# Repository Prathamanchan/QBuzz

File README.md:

# QBuzz
QBuzz Final Project 
Upload the code to arduino and run

$ python qbuzz.py

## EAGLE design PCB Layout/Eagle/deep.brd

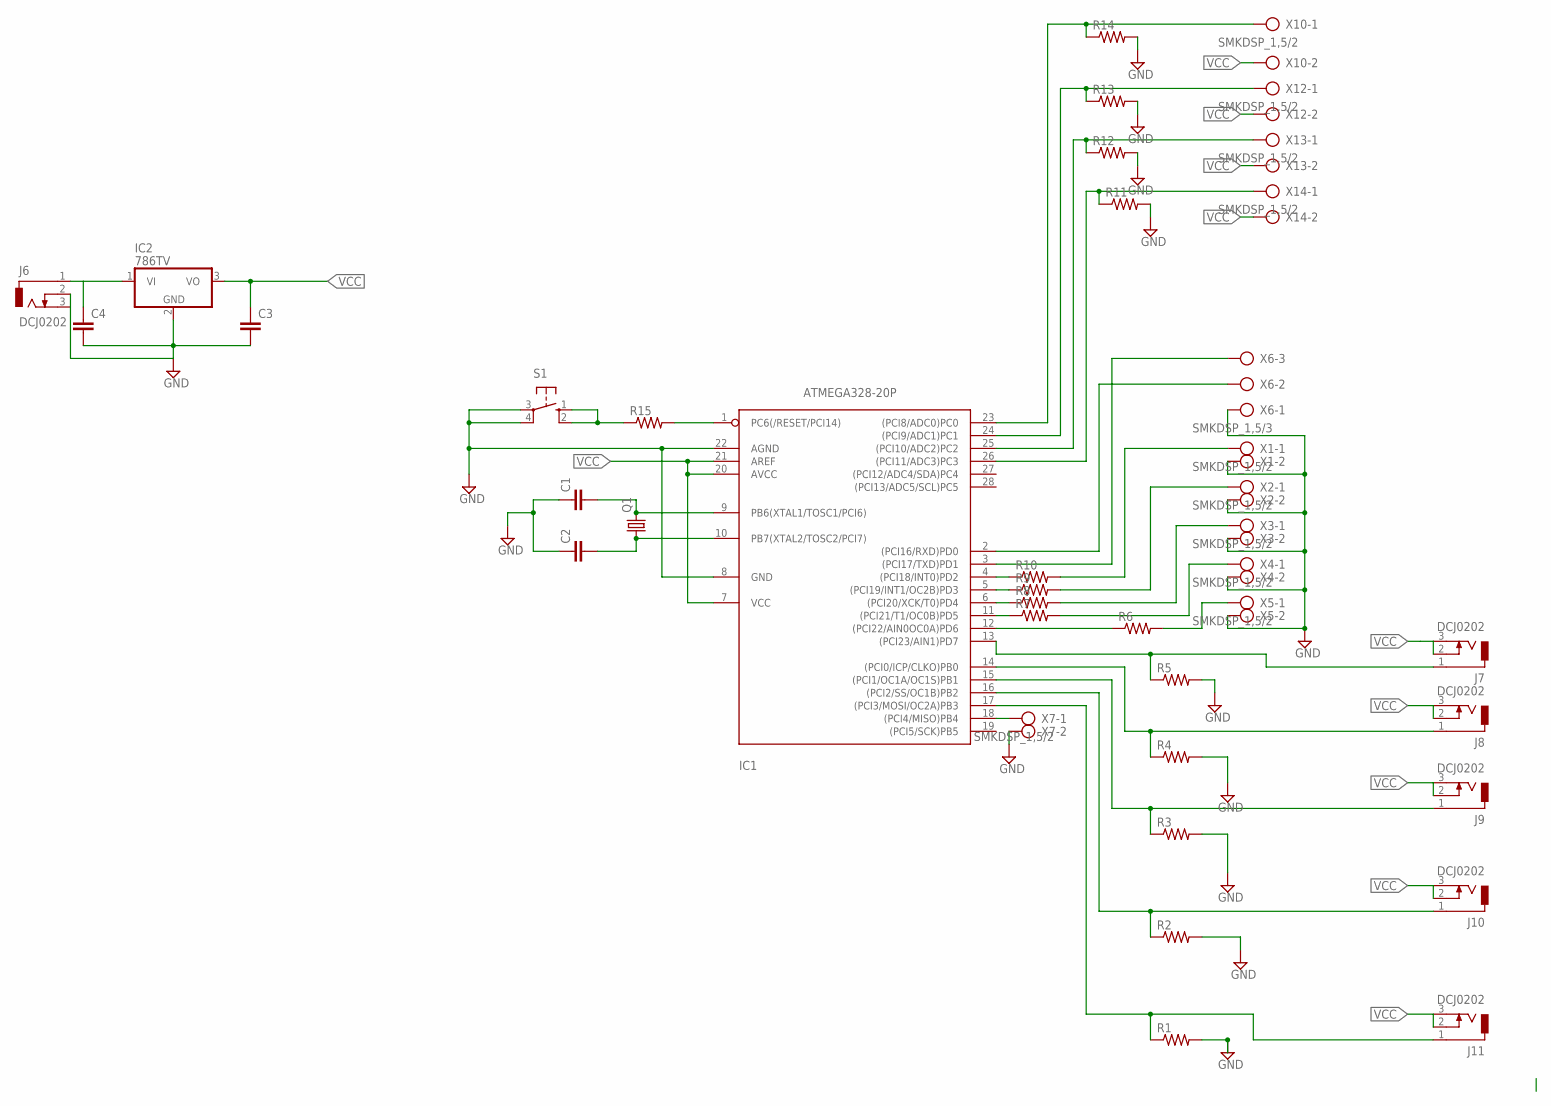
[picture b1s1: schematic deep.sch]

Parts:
C1, C2: C-EU025-030X050; C025-030X050
C3, C4: C-EU025-025X050; C025-025X050
IC1: ATMEGA328-20P; DIL28-3
IC2: 786TV; TO220V
J6, J7, J8, J9, J10, J11: DCJ0202
Q1: CRYSTALHC49U70; HC49U70
R1, R2, R3, R4, R5, R6, R7, R8, R9, R10, R11, R12, R13, R14, R15: R-US_0207/10; 0207/10
S1: 10-XX; B3F-10XX
X1, X2, X3, X4, X5, X7, X10, X12, X13, X14: SMKDSP_1,5/2
X6: SMKDSP_1,5/3

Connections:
GND: C1.1, C2.1, C3.2, C4.2, IC1.8 (GND), IC1.22 (AGND), IC2.2 (GND), J6.2, J6.3, R1.2, R2.2, R3.2, R4.2, R5.2, R11.2, R12.2, R13.2, R14.2, S1.3, S1.4 (P1), X1.2, X2.2, X3.2, X4.2, X5.2, X6.1, X7.2
unnamed: C1.2, IC1.9 (PB6(XTAL1/TOSC1/PCI6)), Q1.2
unnamed: C2.2, IC1.10 (PB7(XTAL2/TOSC2/PCI7)), Q1.1
unnamed: IC1.1 (PC6(/RESET/PCI14)), R15.2
unnamed: R15.1, S1.1 (S), S1.2 (S1)
unnamed: IC1.12 ((PCI22/AIN0OC0A)PD6), R6.1
unnamed: IC1.11 ((PCI21/T1/OC0B)PD5), R7.1
unnamed: IC1.6 ((PCI20/XCK/T0)PD4), R8.1
unnamed: IC1.5 ((PCI19/INT1/OC2B)PD3), R9.1
unnamed: IC1.4 ((PCI18/INT0)PD2), R10.1
unnamed: IC1.2 ((PCI16/RXD)PD0), X6.2
unnamed: IC1.14 ((PCI0/ICP/CLKO)PB0), J8.1, R4.1
unnamed: IC1.15 ((PCI1/OC1A/OC1S)PB1), J9.1, R3.1
unnamed: IC1.16 ((PCI2/SS/OC1B)PB2), J10.1, R2.1
unnamed: IC1.17 ((PCI3/MOSI/OC2A)PB3), J11.1, R1.1
unnamed: R10.2, X1.1
unnamed: R9.2, X2.1
unnamed: R8.2, X3.1
unnamed: R7.2, X4.1
unnamed: R6.2, X5.1
unnamed: IC1.3 ((PCI17/TXD)PD1), X6.3
unnamed: IC1.24 ((PCI9/ADC1)PC1), R13.1, X12.1
unnamed: IC1.13 ((PCI23/AIN1)PD7), J7.1, R5.1
unnamed: C4.1, IC2.1 (VI), J6.1
unnamed: IC1.18 ((PCI4/MISO)PB4), X7.1
unnamed: IC1.23 ((PCI8/ADC0)PC0), R14.1, X10.1
unnamed: J7.2, J7.3
unnamed: IC1.25 ((PCI10/ADC2)PC2), R12.1, X13.1
unnamed: IC1.26 ((PCI11/ADC3)PC3), R11.1, X14.1
VCC: C3.1, IC1.7 (VCC), IC1.20 (AVCC), IC1.21 (AREF), IC2.3 (VO), J8.2, J8.3, J9.2, J9.3, J10.2, J10.3, J11.2, J11.3, X10.2, X12.2, X13.2, X14.2

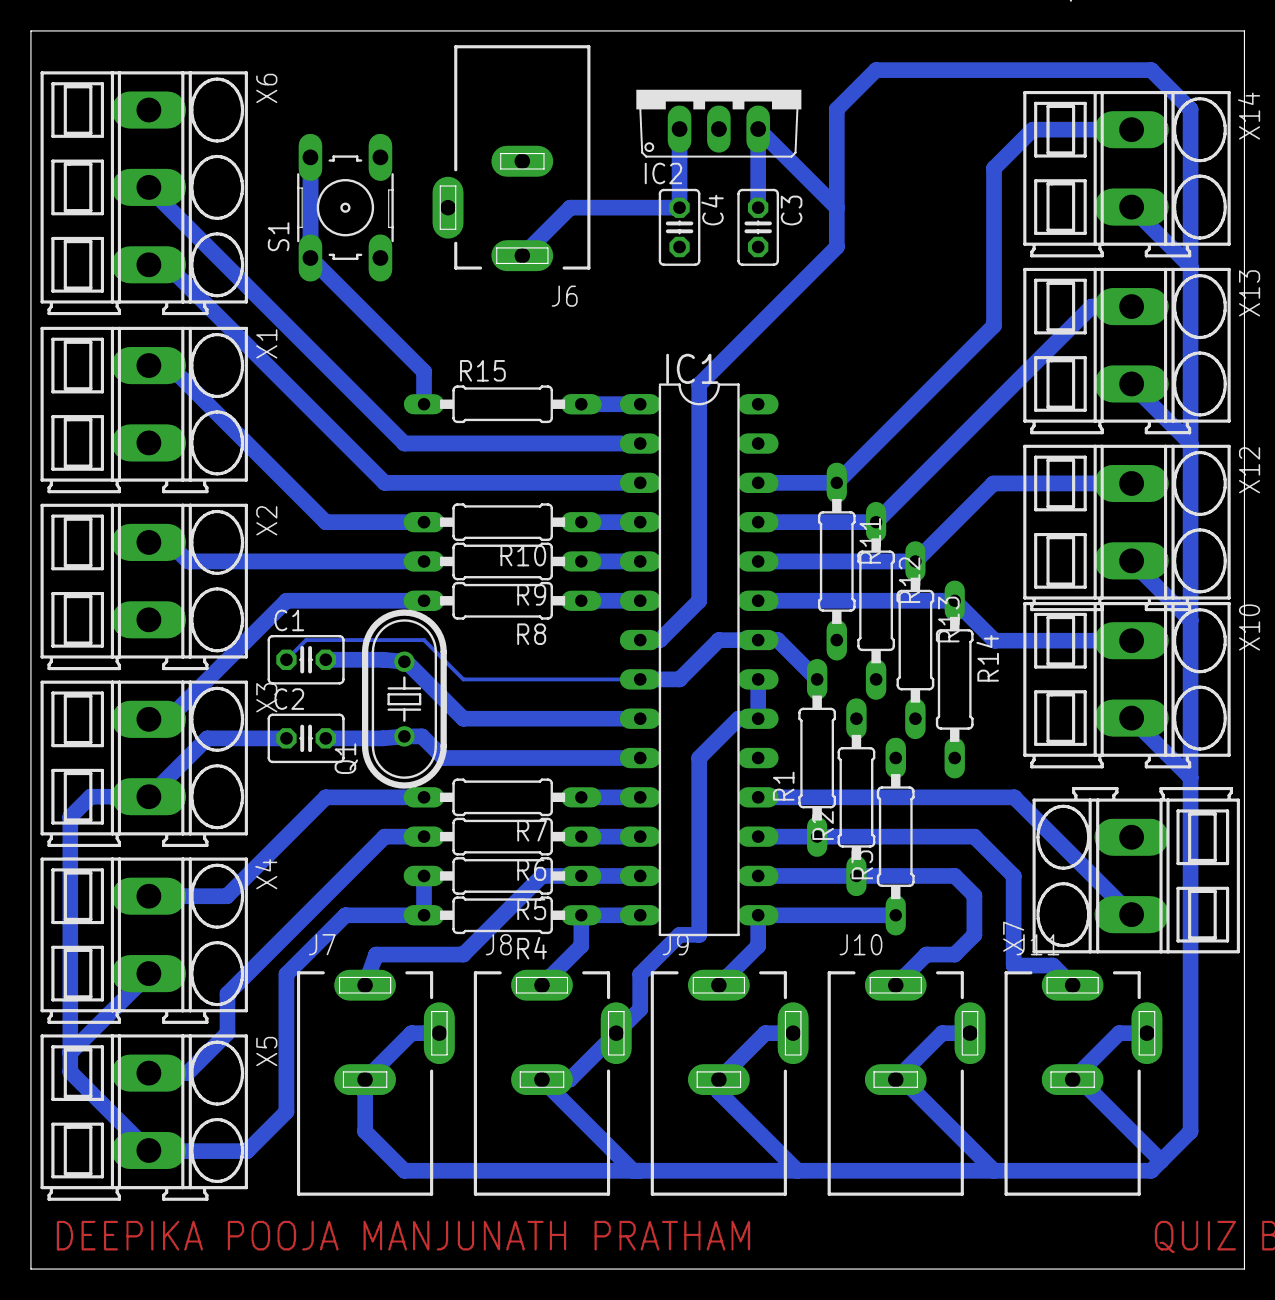
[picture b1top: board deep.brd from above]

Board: 2 copper layers, 78.4 x 80.0 mm, 40 parts (0 on the bottom side), 30 nets.

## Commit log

2018-10-12 Code Updated
2018-10-17 Push up
2018-10-25 Update Everything
